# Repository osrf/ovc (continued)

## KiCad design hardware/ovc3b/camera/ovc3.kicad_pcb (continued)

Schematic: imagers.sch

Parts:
C16, C17, C20, C21: 1u; C_0402_1005Metric; MPN CL05A105KA5NQNC
C22, C23, C24, C25, C32, C33, C34, C35, C42, C43, C45, C46: 10u; C_0402_1005Metric; MPN CL05A106MP8NUB8
C26, C27, C28, C29, C30, C31, C36, C37, C38, C39, C40, C41, C44, C47, C48, C49, C50, C51, C54, C55, C56, C57, C58, C59, C60, C61, C62, C63, C64, C65: 100n; C_0402_1005Metric; MPN CL05F104ZO5NNNC
J1: LEFT_LENS; LENS_HOLDER_20MM_PT-LH010M; MPN DNP
J2: RIGHT_LENS; LENS_HOLDER_20MM_PT-LH010M; MPN DNP
J4: MIDDLE_LENS; LENS_HOLDER_20MM_PT-LH010M; MPN DNP
J11: CAM2_TIMING_DEBUG; PinHeader_1x05_P2.00mm_Vertical; MPN DNP
U1, U2: AR0144CS; BGA-72_9x8_5.545x5.565mm; MPN AR0144CSSM00SUKA0-CPBR2
U4: AR0144CS; BGA-72_9x8_5.545x5.565mm; MPN AR0144CSSC00SUKA0-CPBR2
U10, U12: LP5907MFX-2.8; SOT-23-5; MPN LP5907MFX-2.8/NOPB

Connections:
+1V2: C24.1, C26.1, C29.1, C31.1, C34.1, C36.1, C39.1, C41.1, C44.1, C46.1, C49.1, C51.1, C60.1, C61.1, C62.1, C63.1, C64.1, C65.1, U1.A3 (DVDD), U1.B2 (DVDD), U1.C5 (DVDD_PHY), U1.C6 (DVDD), U1.D8 (DVDD), U1.F2 (DVDD), U1.G4 (DVDD), U1.G5 (DVDD), U1.G6 (DVDD), U2.A3 (DVDD), U2.B2 (DVDD), U2.C5 (DVDD_PHY), U2.C6 (DVDD), U2.D8 (DVDD), U2.F2 (DVDD), U2.G4 (DVDD), U2.G5 (DVDD), U2.G6 (DVDD), U4.A3 (DVDD), U4.B2 (DVDD), U4.C5 (DVDD_PHY), U4.C6 (DVDD), U4.D8 (DVDD), U4.F2 (DVDD), U4.G4 (DVDD), U4.G5 (DVDD), U4.G6 (DVDD); also elsewhere on the board
+1V8: C25.1, C30.1, C35.1, C40.1, C45.1, C50.1, C57.1, C58.1, C59.1, U1.A2 (VDDIO), U1.B8 (VDDIO), U1.C2 (VDDIO), U1.C8 (VDDIO), U1.E3 (VDDIO), U2.A2 (VDDIO), U2.B8 (VDDIO), U2.C2 (VDDIO), U2.C8 (VDDIO), U2.E3 (VDDIO), U4.A2 (VDDIO), U4.B8 (VDDIO), U4.C2 (VDDIO), U4.C8 (VDDIO), U4.E3 (VDDIO); also elsewhere on the board
/imagers/CAM0_2V8: C17.1, C22.1, C23.1, C27.1, C28.1, C54.1, U1.F9 (VAA_PIX), U1.G2 (VAA), U1.G8 (VAA), U1.H1 (VAA), U1.H2 (VAA), U1.H8 (VAA), U1.H9 (VAA), U10.5
/imagers/CAM1_2V8: C21.1, C32.1, C33.1, C37.1, C38.1, C42.1, C43.1, C47.1, C48.1, C55.1, C56.1, U2.F9 (VAA_PIX), U2.G2 (VAA), U2.G8 (VAA), U2.H1 (VAA), U2.H2 (VAA), U2.H8 (VAA), U2.H9 (VAA), U4.F9 (VAA_PIX), U4.G2 (VAA), U4.G8 (VAA), U4.H1 (VAA), U4.H2 (VAA), U4.H8 (VAA), U4.H9 (VAA), U12.5
CAM0_CLK+: U1.A5 (CLK+); also elsewhere on the board
CAM0_CLK-: U1.B5 (CLK-); also elsewhere on the board
CAM0_D0+: U1.A6 (DATA0+); also elsewhere on the board
CAM0_D0-: U1.B6 (DATA0-); also elsewhere on the board
CAM0_D1+: U1.A4 (DATA1+)
CAM0_D1-: U1.B4 (DATA1-)
CAM0_EXTCLK_1V8: U1.B3 (EXTCLK); also elsewhere on the board
CAM0_SCL_1V8: U1.C7 (SCL); also elsewhere on the board
CAM0_SDA_1V8: U1.E6 (SDA); also elsewhere on the board
CAM0_TRIG_1V8: U1.E7 (TRIGGER); also elsewhere on the board
CAM0_nRESET_1V8: U1.G1 (~RESET); also elsewhere on the board
CAM1_CLK+: U2.A5 (CLK+); also elsewhere on the board
CAM1_CLK-: U2.B5 (CLK-); also elsewhere on the board
CAM1_D0+: U2.A6 (DATA0+); also elsewhere on the board
CAM1_D0-: U2.B6 (DATA0-); also elsewhere on the board
CAM1_D1+: U2.A4 (DATA1+)
CAM1_D1-: U2.B4 (DATA1-)
CAM1_EXTCLK_1V8: U2.B3 (EXTCLK); also elsewhere on the board
CAM1_SCL_1V8: U2.C7 (SCL); also elsewhere on the board
CAM1_SDA_1V8: U2.E6 (SDA); also elsewhere on the board
CAM1_TRIG_1V8: U2.E7 (TRIGGER); also elsewhere on the board
CAM1_nRESET_1V8: U2.G1 (~RESET); also elsewhere on the board
CAM2_CLK+: U4.A5 (CLK+); also elsewhere on the board
CAM2_CLK-: U4.B5 (CLK-); also elsewhere on the board
CAM2_D0+: U4.A6 (DATA0+); also elsewhere on the board
CAM2_D0-: U4.B6 (DATA0-); also elsewhere on the board
CAM2_D1+: U4.A4 (DATA1+)
CAM2_D1-: U4.B4 (DATA1-)
CAM2_EXTCLK_1V8: U4.B3 (EXTCLK); also elsewhere on the board
CAM2_FLASH_1V8: J11.3, U4.F6 (FLASH)
CAM2_SCL_1V8: J11.1, U4.C7 (SCL); also elsewhere on the board
CAM2_SDA_1V8: J11.2, U4.E6 (SDA); also elsewhere on the board
CAM2_TRIG_1V8: J11.4, U4.E7 (TRIGGER); also elsewhere on the board
CAM2_nRESET_1V8: U4.G1 (~RESET); also elsewhere on the board
GND: C16.2, C17.2, C20.2, C21.2, C22.2, C23.2, C24.2, C25.2, C26.2, C27.2, C28.2, C29.2, C30.2, C31.2, C32.2, C33.2, C34.2, C35.2, C36.2, C37.2, C38.2, C39.2, C40.2, C41.2, C42.2, C43.2, C44.2, C45.2, C46.2, C47.2, C48.2, C49.2, C50.2, C51.2, C54.2, C55.2, C56.2, C57.2, C58.2, C59.2, C60.2, C61.2, C62.2, C63.2, C64.2, C65.2, J1.1, J2.1, J4.1, J11.5, U1.A1 (DGND), U1.A8 (TEST), U1.B7 (SADDR), U1.D5 (DGND), U1.D6 (DGND), U1.D7 (~OUTPUT_EN), U1.D9 (AGND), U1.E8 (DGND), U1.F1 (DGND), U1.F7 (DGND), U1.F8 (DGND), U1.G3 (AGND), U1.G7 (AGND), U1.H3 (AGND), U1.H4 (DGND), U1.H5 (DGND), U1.H6 (DGND), U1.H7 (AGND), U2.A1 (DGND), U2.A8 (TEST), U2.B7 (SADDR), U2.D5 (DGND), U2.D6 (DGND), U2.D7 (~OUTPUT_EN), U2.D9 (AGND), U2.E8 (DGND), U2.F1 (DGND), U2.F7 (DGND), U2.F8 (DGND), U2.G3 (AGND), U2.G7 (AGND), U2.H3 (AGND), U2.H4 (DGND), U2.H5 (DGND), U2.H6 (DGND), U2.H7 (AGND), U4.A1 (DGND), U4.A8 (TEST), U4.B7 (SADDR), U4.D5 (DGND), U4.D6 (DGND), U4.D7 (~OUTPUT_EN), U4.D9 (AGND), U4.E8 (DGND), U4.F1 (DGND), U4.F7 (DGND), U4.F8 (DGND), U4.G3 (AGND), U4.G7 (AGND), U4.H3 (AGND), U4.H4 (DGND), U4.H5 (DGND), U4.H6 (DGND), U4.H7 (AGND), U10.2, U12.2; also elsewhere on the board

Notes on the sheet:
VDD is 1.2V, VAA is 2.8V, VDD_IO is 1.8V
RGB sensor

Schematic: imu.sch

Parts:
C11, C12, C13: 100n; C_0402_1005Metric; MPN CL05F104ZO5NNNC
U3: ICM-20948; InvenSense_QFN-24_3x3mm_P0.4mm; MPN ICM-20948

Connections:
+1V8: C11.1, U3.8 (VDDIO); also elsewhere on the board
GND: C11.2, C12.2, C13.2, U3.18 (GND), U3.20 (GND); also elsewhere on the board
ICM_IMU_INT1_1V8: U3.12 (INT1); also elsewhere on the board
ICM_IMU_SYNC_1V8: U3.11 (FSYNC); also elsewhere on the board
ICM_SPI_CLK_1V8: U3.23 (SCL/SCLK); also elsewhere on the board
ICM_SPI_CS_1V8: U3.22 (~CS); also elsewhere on the board
ICM_SPI_MISO_1V8: U3.9 (SDO/AD0); also elsewhere on the board
ICM_SPI_MOSI_1V8: U3.24 (SDA/SDI); also elsewhere on the board
unnamed: C13.1, U3.10 (REGOUT)

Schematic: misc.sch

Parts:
C10: 100n; C_0603_1608Metric; MPN CL10B104KB8NNNC
C80, C81: 100n; C_0402_1005Metric; MPN CL05F104ZO5NNNC
D1, D7: LED; LED_0402_1005Metric; MPN VLMS1500-GS08
D2, D8: LED; LED_0402_1005Metric; MPN VLMG1500-GS08
J5: LOW_SPEED_EXP; PinHeader_2x15_P1.27mm_Vertical; MPN DNP
J7: Micro_SD_Card_Det_Hirose_DM3BT; microSD_HC_Hirose_DM3BT-DSF-PEJS; MPN DM3BT-DSF-PEJS
R14, R15, R29, R30: 330R; R_0402_1005Metric; MPN ERJ-2GEJ331X
U9: ARJ11C-MBSAS-A-BA-7MU2; MPN ARJ11C-MBSAS-A-BA-7MU2
U13: TXS02612; TI_RTW0024B; MPN TXS02612RTWR

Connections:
+1V2: J5.12, J5.14; also elsewhere on the board
+1V8: J5.1, J5.2; also elsewhere on the board
/misc/LS_CLK: J7.5, U13.19 (CLKB0)
/misc/LS_CMD: J7.3, U13.23 (DAT2B0)
/misc/LS_DAT0: J7.7, U13.22 (DAT3B0)
/misc/LS_DAT1: J7.8, U13.20 (CMDB0)
/misc/LS_DAT2: J7.1, U13.18 (DAT0B0)
/misc/LS_DAT3: J7.2, U13.16 (DAT1B0)
ETH_VCC: C10.1, U9.5 (CT), U9.6 (CT); also elsewhere on the board
GND: C10.2, C80.2, C81.2, D1.1 (K), D2.1 (K), D7.1 (K), D8.1 (K), J5.4, J5.10, J5.16, J5.30, J7.6, J7.11, U9.11 (GRNYEL_C), U9.14 (GRN_C), U9.MNT, U9.SHLD, U13.2 (GND), U13.11 (GND), U13.24 (SEL), U13.25 (PAD); also elsewhere on the board
GPIO0: J5.3; also elsewhere on the board
GPIO1: J5.5; also elsewhere on the board
GPIO2: J5.7; also elsewhere on the board
GPIO3: J5.9; also elsewhere on the board
GPIO4: J5.11; also elsewhere on the board
GPIO5: J5.13; also elsewhere on the board
GPIO6: J5.15; also elsewhere on the board
GPIO7: J5.17; also elsewhere on the board
GPIO8: J5.19; also elsewhere on the board
GPIO9: J5.21; also elsewhere on the board
GPIO10: J5.23; also elsewhere on the board
GPIO11: J5.25; also elsewhere on the board
GPIO12: J5.18; also elsewhere on the board
GPIO13: J5.20; also elsewhere on the board
GPIO14: J5.22; also elsewhere on the board
GPIO15: J5.24; also elsewhere on the board
GPIO16: J5.26; also elsewhere on the board
GPIO17: J5.28; also elsewhere on the board
GPIO18: J5.27; also elsewhere on the board
GPIO19: J5.29; also elsewhere on the board
LED0: R14.2; also elsewhere on the board
LED1: R15.2; also elsewhere on the board
LED2: R29.2; also elsewhere on the board
LED3: R30.2; also elsewhere on the board
unnamed: D1.2 (A), R14.1
unnamed: D2.2 (A), R15.1
unnamed: D7.2 (A), R29.1
unnamed: D8.2 (A), R30.1
PHY_MDI0_N: U9.2 (TRD0-); also elsewhere on the board
PHY_MDI0_P: U9.1 (TRD0+); also elsewhere on the board
PHY_MDI1_N: U9.4 (TRD1-); also elsewhere on the board
PHY_MDI1_P: U9.3 (TRD1+); also elsewhere on the board
PHY_MDI2_N: U9.8 (TRD2-); also elsewhere on the board
PHY_MDI2_P: U9.7 (TRD2+); also elsewhere on the board
PHY_MDI3_N: U9.10 (TRD3-); also elsewhere on the board
PHY_MDI3_P: U9.9 (TRD3+); also elsewhere on the board
SD_CLK: U13.9 (CLKA); also elsewhere on the board
SD_CMD: U13.1 (DAT2A); also elsewhere on the board
SD_DAT0: U13.3 (DAT3A); also elsewhere on the board
SD_DAT1: U13.4 (CMDA); also elsewhere on the board
SD_DAT2: U13.6 (DAT0A); also elsewhere on the board
SD_DAT3: U13.7 (DAT1A); also elsewhere on the board

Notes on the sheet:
not enough easily-routed high-voltage i/o for now, so leaving the LEDs open...

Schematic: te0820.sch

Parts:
C14, C15, C53, C69, C70, C71, C72, C73, C74, C85: 100n; C_0402_1005Metric; MPN CL05F104ZO5NNNC
CONN1: Trenz_conn_dummy; MPN LSHM-130-04.0-L-DV-A-S-K-TR
CONN2, CONN3: Trenz_conn_dummy; MPN LSHM-150-04.0-L-DV-A-S-K-TR
J6: FRONT_PACK; PinHeader_2x08_P2.00mm_Vertical; MPN Sullins
M1: TE0820; MPN DNP
R9, R16, R17, R18, R19, R20: 2k2; R_0402_1005Metric; MPN RC0402FR-072K2L
R12, R13, R21, R22, R26: 10k; R_0402_1005Metric; MPN ERA-2AED103X
R27: 1k; R_0402_1005Metric; MPN ERJ-2RKF1001X
SW1: SW_DIP_x04; SW_DIP_SPSTx04_Slide_6.7x11.72mm_W8.61mm_P2.54mm_LowProfile; MPN 418121270804
U8: SN74AXC4T245; TSSOP-16_4.4x5mm_P0.65mm; MPN SN74AXC4T245PWR
U16: SN74AXCH8T245; TSSOP-24_4.4x7.8mm_P0.65mm; MPN SN74AXCH8T245PWR
U17, U18: TCA9803; VSSOP-8_3.0x3.0mm_P0.65mm; MPN TCA9803DGKR

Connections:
3V3_VOUT: M1.JB2.9 (3.3V), M1.JB2.11 (3.3V); also elsewhere on the board
+1V2: C14.1, C69.1, C70.1, C73.1, J6.4, M1.JB1.10 (VCC_66), M1.JB1.12 (VCC_66), M1.JB2.8 (VCCO_64), M1.JB2.10 (VCCO_64), R17.1, R18.1, R19.1, R20.1, U8.1 (VCCA), U8.3 (2DIR), U16.1 (VCCA), U16.2 (DIR1), U17.1 (VCCA), U17.5 (EN), U18.1 (VCCA), U18.5 (EN); also elsewhere on the board
+1V8: C15.1, C71.1, C72.1, C74.1, M1.JB1.40 (1.8V), M1.JB2.6 (VCCO_65), R9.1, R13.1, R16.1, R21.1, R22.1, U8.16 (VCCB), U16.23 (VCCB), U16.24 (VCCB), U17.8 (VCCB), U18.8 (VCCB); also elsewhere on the board
/te0820/CAM1_EXTCLK_1V2: M1.JB1.42 (G3_B66_L4_P), U16.8 (A6)
/te0820/CAM1_SCL_1V2: M1.JB1.34 (G5_B66_L6_P), R18.2, U17.2 (SCLA)
/te0820/CAM1_SDA_1V2: M1.JB1.32 (F5_B66_L6_N), R17.2, U17.3 (SDAA)
/te0820/CAM1_TRIG_1V2: M1.JB1.36 (C8_B66_L22_P), U16.10 (A8)
/te0820/CAM1_nRESET_1V2: M1.JB1.38 (B8_B66_L22_N), U16.9 (A7)
/te0820/CAM2_EXTCLK_1V2: M1.JB1.50 (B1_B66_L7_N), U16.4 (A2)
/te0820/CAM2_SCL_1V2: M1.JB1.84 (A1_B66_L8_N), R20.2, U18.2 (SCLA)
/te0820/CAM2_SDA_1V2: M1.JB1.82 (A2_B66_L8_P), R19.2, U18.3 (SDAA)
/te0820/CAM2_TRIG_1V2: M1.JB1.52 (C1_B66_L7_P), U16.3 (A1)
/te0820/CAM2_nRESET_1V2: M1.JB1.48 (C6_B66_L20_P), U16.5 (A3)
/te0820/DIPSWITCH: M1.JB3.47 (U9_B65_L2_P), R22.2, SW1.5
/te0820/ICM_IMU_INT1_1V2: M1.JB1.77 (A9_B66_L23_P), U8.5 (1A2)
/te0820/ICM_SPI_CLK_1V2: M1.JB1.44 (F3_B66_L4_N), U16.7 (A5)
/te0820/ICM_SPI_CS_1V2: M1.JB1.46 (B6_B66_L20_N), U16.6 (A4)
/te0820/ICM_SPI_MISO_1V2: M1.JB1.75 (A8_B66_L23_N), U8.4 (1A1)
/te0820/ICM_SPI_MOSI_1V2: M1.JB1.76 (C2_B66_L12_N), U8.7 (2A2)
/te0820/ICM_SPI_SYNC_1V2: M1.JB1.78 (C3_B66_L12_P), U8.6 (2A1)
/te0820/JTAGEN: M1.JB1.90 (JTAGEN), R21.2, SW1.6
/te0820/MODE: M1.JB1.31 (MODE), R13.2, SW1.7
/te0820/NOSEQ: M1.JB1.8 (NOSEQ), R12.2, SW1.8
BONUS1_CLK0+: M1.JB2.35 (AC9_B64_L1_P); also elsewhere on the board
BONUS1_CLK0-: M1.JB2.37 (AD9_B64_L1_N); also elsewhere on the board
BONUS1_CLK1+: M1.JB2.62 (AD2_B64_L16_P); also elsewhere on the board
BONUS1_CLK1-: M1.JB2.64 (AD1_B64_L16_N); also elsewhere on the board
BONUS1_DAT0+: M1.JB2.41 (AE9_B64_L2_P); also elsewhere on the board
BONUS1_DAT0-: M1.JB2.43 (AE8_B64_L2_N); also elsewhere on the board
BONUS1_DAT1+: M1.JB2.46 (AB2_B64_L17_P); also elsewhere on the board
BONUS1_DAT1-: M1.JB2.48 (AC2_B64_L17_N); also elsewhere on the board
BONUS1_EXTCLK: M1.JB2.44 (AB4_B64_L15_P); also elsewhere on the board
BONUS1_FLASH: M1.JB2.78 (AG5_B64_L10_N); also elsewhere on the board
BONUS1_RESET: M1.JB2.76 (AG6_B64_L10_P); also elsewhere on the board
BONUS1_SCL0: M1.JB2.56 (AB1_B64_L18_P); also elsewhere on the board
BONUS1_SCL1: M1.JB2.66 (AE3_B64_L21_P); also elsewhere on the board
BONUS1_SDA0: M1.JB2.58 (AC1_B64_L18_N); also elsewhere on the board
BONUS1_SDA1: M1.JB2.68 (AF3_B64_L21_N); also elsewhere on the board
BONUS1_TRIGGER: M1.JB2.42 (AB3_B64_L15_N); also elsewhere on the board
BONUS2_CLK0+: M1.JB1.67 (D7_B66_L13_P); also elsewhere on the board
BONUS2_CLK0-: M1.JB1.65 (D6_B66_L13_N); also elsewhere on the board
BONUS2_CLK1+: M1.JB1.39 (G8_B66_L16_P); also elsewhere on the board
BONUS2_CLK1-: M1.JB1.41 (F7_B66_L16_N); also elsewhere on the board
BONUS2_DAT0+: M1.JB1.62 (E5_B66_L14_P); also elsewhere on the board
BONUS2_DAT0-: M1.JB1.60 (D5_B66_L14_N); also elsewhere on the board
BONUS2_DAT1+: M1.JB1.47 (F8_B66_L17_P); also elsewhere on the board
BONUS2_DAT1-: M1.JB1.45 (E8_B66_L17_N); also elsewhere on the board
BONUS2_EXTCLK: M1.JB1.61 (E3_B66_L5_N); also elsewhere on the board
BONUS2_FLASH: M1.JB1.49 (G6_B66_L15_P); also elsewhere on the board
BONUS2_RESET: M1.JB1.37 (D9_B66_L18_N); also elsewhere on the board
BONUS2_SCL0: M1.JB1.59 (E4_B66_L5_P); also elsewhere on the board
BONUS2_SCL1: M1.JB1.55 (F2_B66_L3_P); also elsewhere on the board
BONUS2_SDA0: M1.JB1.57 (E2_B66_L3_N); also elsewhere on the board
BONUS2_SDA1: M1.JB1.51 (F6_B66_L15_N); also elsewhere on the board
BONUS2_TRIGGER: M1.JB1.35 (E9_B66_L18_P); also elsewhere on the board
BONUS3_CLK0+: M1.JB2.61 (AG9_B64_L7_P); also elsewhere on the board
BONUS3_CLK0-: M1.JB2.63 (AH9_B64_L7_N); also elsewhere on the board
BONUS3_CLK1+: M1.JB2.77 (AD7_B64_L4_P); also elsewhere on the board
BONUS3_CLK1-: M1.JB2.75 (AE7_B64_L4_N); also elsewhere on the board
BONUS3_DAT0+: M1.JB2.65 (AF8_B64_L8_P); also elsewhere on the board
BONUS3_DAT0-: M1.JB2.67 (AG8_B64_L8_N); also elsewhere on the board
BONUS3_DAT1+: M1.JB2.81 (AB7_B64_L5_P); also elsewhere on the board
BONUS3_DAT1-: M1.JB2.83 (AC7_B64_L5_N); also elsewhere on the board
BONUS3_EXTCLK: M1.JB2.31 (AB8_B64_L3_P); also elsewhere on the board
BONUS3_FLASH: M1.JB2.53 (AF5_B64_L12_N); also elsewhere on the board
BONUS3_RESET: M1.JB2.71 (AH8_B64_L9_P); also elsewhere on the board
BONUS3_SCL0: M1.JB2.33 (AC8_B64_L3_N); also elsewhere on the board
BONUS3_SCL1: M1.JB2.47 (AF6_B64_L11_N); also elsewhere on the board
BONUS3_SDA0: M1.JB2.45 (AF7_B64_L11_P); also elsewhere on the board
BONUS3_SDA1: M1.JB2.51 (AE5_B64_L12_P); also elsewhere on the board
BONUS3_TRIGGER: M1.JB2.73 (AH7_B64_L9_N); also elsewhere on the board
BONUS4_CLK0+: M1.JB2.72 (AE2_B64_L22_P); also elsewhere on the board
BONUS4_CLK0-: M1.JB2.74 (AF2_B64_L22_N); also elsewhere on the board
BONUS4_CLK1+: M1.JB2.82 (AG4_B64_L19_P); also elsewhere on the board
BONUS4_CLK1-: M1.JB2.84 (AH4_B64_L19_N); also elsewhere on the board
BONUS4_DAT0+: M1.JB2.95 (AH2_B64_L23_P); also elsewhere on the board
BONUS4_DAT0-: M1.JB2.97 (AH1_B64_L23_N); also elsewhere on the board
BONUS4_DAT1+: M1.JB2.86 (AG3_B64_L20_P); also elsewhere on the board
BONUS4_DAT1-: M1.JB2.88 (AH3_B64_L20_N); also elsewhere on the board
BONUS4_EXTCLK: M1.JB1.69 (C9_B66_L24_P); also elsewhere on the board
BONUS4_FLASH: M1.JB1.87 (B5_B66_L19_P); also elsewhere on the board
BONUS4_RESET: M1.JB1.97 (A3_B66_L9_N); also elsewhere on the board
BONUS4_SCL0: M1.JB1.71 (B9_B66_L24_N); also elsewhere on the board
BONUS4_SCL1: M1.JB1.81 (A6_B66_L21_N); also elsewhere on the board
BONUS4_SDA0: M1.JB1.79 (A7_B66_L21_P); also elsewhere on the board
BONUS4_SDA1: M1.JB1.85 (A5_B66_L19_N); also elsewhere on the board
BONUS4_TRIGGER: M1.JB1.99 (B3_B66_L9_P); also elsewhere on the board
CAM0_CLK+: M1.JB2.55 (AD5_B64_L13_P); also elsewhere on the board
CAM0_CLK-: M1.JB2.57 (AD4_B64_L13_N); also elsewhere on the board
CAM0_D0+: M1.JB2.52 (AC4_B64_L14_P); also elsewhere on the board
CAM0_D0-: M1.JB2.54 (AC3_B64_L14_N); also elsewhere on the board
CAM0_EXTCLK_1V8: M1.JB2.15 (P6_B65_L16_N); also elsewhere on the board
CAM0_SCL_1V8: M1.JB2.21 (L1_B65_L7_P), R16.2; also elsewhere on the board
CAM0_SDA_1V8: M1.JB2.23 (K1_B65_L7_N), R9.2; also elsewhere on the board
CAM0_TRIG_1V8: M1.JB2.27 (N6_B65_L15_N); also elsewhere on the board
CAM0_nRESET_1V8: M1.JB2.25 (N7_B65_L15_P); also elsewhere on the board
CAM1_CLK+: M1.JB1.70 (G1_B66_L1_P); also elsewhere on the board
CAM1_CLK-: M1.JB1.72 (F1_B66_L1_N); also elsewhere on the board
CAM1_D0+: M1.JB1.58 (E1_B66_L2_P); also elsewhere on the board
CAM1_D0-: M1.JB1.56 (D1_B66_L2_N); also elsewhere on the board
CAM1_EXTCLK_1V8: U16.16 (B6); also elsewhere on the board
CAM1_SCL_1V8: U17.7 (SCLB); also elsewhere on the board
CAM1_SDA_1V8: U17.6 (SDAB); also elsewhere on the board
CAM1_TRIG_1V8: U16.14 (B8); also elsewhere on the board
CAM1_nRESET_1V8: U16.15 (B7); also elsewhere on the board
CAM2_CLK+: M1.JB1.95 (B4_B66_L10_P); also elsewhere on the board
CAM2_CLK-: M1.JB1.93 (A4_B66_L10_N); also elsewhere on the board
CAM2_D0+: M1.JB1.68 (D4_B66_L11_P); also elsewhere on the board
CAM2_D0-: M1.JB1.66 (C4_B66_L11_N); also elsewhere on the board
CAM2_EXTCLK_1V8: U16.20 (B2); also elsewhere on the board
CAM2_SCL_1V8: U18.7 (SCLB); also elsewhere on the board
CAM2_SDA_1V8: U18.6 (SDAB); also elsewhere on the board
CAM2_TRIG_1V8: U16.21 (B1); also elsewhere on the board
CAM2_nRESET_1V8: U16.19 (B3); also elsewhere on the board
ETH_VCC: M1.JB1.13 (PHY_COM); also elsewhere on the board
FRONT_AUX0: J6.3, M1.JB2.85 (AB6_B64_L6_P)
FRONT_AUX1: J6.5, M1.JB2.87 (AC6_B64_L6_N)
FRONT_AUX2: J6.7, M1.JB2.91 (AF1_B64_L24_P)
FRONT_AUX3: J6.9, M1.JB2.93 (AG1_B64_L24_N)
FRONT_AUX4: J6.11, M1.JB2.99 (AH6_B64_T1)
FRONT_AUX5: J6.6, M1.JB2.90 (AD6_B64_T0)
GND: C14.2, C15.2, C53.2, C69.2, C70.2, C71.2, C72.2, C73.2, C74.2, C85.2, J6.2, M1.JB1.1 (GND), M1.JB1.7 (GND), M1.JB1.19 (GND), M1.JB1.25 (GND), M1.JB1.30 (GND), M1.JB1.33 (GND), M1.JB1.43 (GND), M1.JB1.53 (GND), M1.JB1.54 (GND), M1.JB1.63 (GND), M1.JB1.64 (GND), M1.JB1.73 (GND), M1.JB1.74 (GND), M1.JB1.83 (GND), M1.JB1.89 (GND), M1.JB2.19 (GND), M1.JB2.29 (GND), M1.JB2.39 (GND), M1.JB2.40 (GND), M1.JB2.49 (GND), M1.JB2.50 (GND), M1.JB2.59 (GND), M1.JB2.60 (GND), M1.JB2.69 (GND), M1.JB2.70 (GND), M1.JB2.79 (GND), M1.JB2.80 (GND), M1.JB2.89 (GND), M1.JB3.5 (GND), M1.JB3.6 (GND), M1.JB3.11 (GND), M1.JB3.12 (GND), M1.JB3.17 (GND), M1.JB3.18 (GND), M1.JB3.23 (GND), M1.JB3.24 (GND), M1.JB3.29 (GND), M1.JB3.30 (GND), M1.JB3.35 (GND), M1.JB3.36 (GND), M1.JB3.45 (GND), M1.JB3.46 (GND), M1.JB3.55 (GND), SW1.1, SW1.2, SW1.3, SW1.4, U8.2 (1DIR), U8.8 (GND), U8.9 (GND), U8.14 (OE#), U8.15 (OE#), U16.11 (DIR2), U16.12 (GND), U16.13 (GND), U16.22 (~OE), U17.4 (GND), U18.4 (GND); also elsewhere on the board
GPIO0: M1.JB2.12 (H9_B65_L24_P); also elsewhere on the board
GPIO1: M1.JB2.14 (H8_B65_L24_N); also elsewhere on the board
GPIO2: M1.JB2.16 (R8_B65_L4_P); also elsewhere on the board
GPIO3: M1.JB2.18 (T8_B65_L4_N); also elsewhere on the board
GPIO4: M1.JB2.22 (M6_B65_L14_P); also elsewhere on the board
GPIO5: M1.JB2.24 (L5_B65_L14_N); also elsewhere on the board
GPIO6: M1.JB2.26 (L3_B65_L12_P); also elsewhere on the board
GPIO7: M1.JB2.28 (L2_B65_L12_N); also elsewhere on the board
GPIO8: M1.JB2.32 (L8_B65_L18_N); also elsewhere on the board
GPIO9: M1.JB2.34 (M8_B65_L18_P); also elsewhere on the board
GPIO10: M1.JB2.36 (J7_B65_L21_P); also elsewhere on the board
GPIO11: M1.JB2.38 (H7_B65_L21_N); also elsewhere on the board
GPIO12: M1.JB3.44 (N8_B65_L17_N); also elsewhere on the board
GPIO13: M1.JB3.42 (N9_B65_L17_P); also elsewhere on the board
GPIO14: M1.JB3.40 (V8_B65_L3_N); also elsewhere on the board
GPIO15: M1.JB3.38 (U8_B65_L3_P); also elsewhere on the board
GPIO16: M1.JB3.37 (W8_B65_L1_P); also elsewhere on the board
GPIO17: M1.JB3.39 (Y8_B65_L1_N); also elsewhere on the board
GPIO18: M1.JB3.41 (R7_B65_L5_P); also elsewhere on the board
GPIO19: M1.JB3.43 (T7_B65_L5_N); also elsewhere on the board
ICM_IMU_INT1_1V8: U8.12 (1B2); also elsewhere on the board
ICM_IMU_SYNC_1V8: U8.11 (2B1); also elsewhere on the board
ICM_SPI_CLK_1V8: U16.17 (B5); also elsewhere on the board
ICM_SPI_CS_1V8: U16.18 (B4); also elsewhere on the board
ICM_SPI_MISO_1V8: U8.13 (1B1); also elsewhere on the board
ICM_SPI_MOSI_1V8: U8.10 (2B2); also elsewhere on the board
JTAG_TCK: J6.14, M1.JB2.100 (C_TCK)
JTAG_TDI: J6.12, M1.JB2.96 (C_TDI)
JTAG_TDO: J6.13, M1.JB2.98 (C_TDO)
JTAG_TMS: J6.15, M1.JB2.94 (C_TMS)
LED0: M1.JB1.94 (J15_MIO27); also elsewhere on the board
LED1: M1.JB1.96 (L15_MIO26); also elsewhere on the board
LED2: M1.JB1.98 (G16_MIO29); also elsewhere on the board
LED3: M1.JB1.100 (K15_MIO28); also elsewhere on the board
unnamed: M1.JB3.52 (OTG-ID), R27.2
unnamed: M1.JB3.56 (USB-VBUS), R26.2
PHY_MDI0_N: M1.JB1.5 (PHY_MDI0_N); also elsewhere on the board
PHY_MDI0_P: M1.JB1.3 (PHY_MDI0_P); also elsewhere on the board
PHY_MDI1_N: M1.JB1.11 (PHY_MDI1_N); also elsewhere on the board
PHY_MDI1_P: M1.JB1.9 (PHY_MDI1_P); also elsewhere on the board
PHY_MDI2_N: M1.JB1.17 (PHY_MDI2_N); also elsewhere on the board
PHY_MDI2_P: M1.JB1.15 (PHY_MDI2_P); also elsewhere on the board
PHY_MDI3_N: M1.JB1.23 (PHY_MDI3_N); also elsewhere on the board
PHY_MDI3_P: M1.JB1.21 (PHY_MDI3_P); also elsewhere on the board
ROOT_RX: J6.10, M1.JB1.91 (F16_MIO30)
ROOT_TX: J6.8, M1.JB1.86 (H16_MIO31)
SD_CLK: M1.JB1.28 (L21_SD_CLK); also elsewhere on the board
SD_CMD: M1.JB1.26 (M19_SD_CMD); also elsewhere on the board
SD_DAT0: M1.JB1.24 (L20_SD_DAT0); also elsewhere on the board
SD_DAT1: M1.JB1.22 (H21_SD_DAT1); also elsewhere on the board
SD_DAT2: M1.JB1.20 (J21_SD_DAT2); also elsewhere on the board
SD_DAT3: M1.JB1.18 (M18_SD_DAT3); also elsewhere on the board
USB2_D+: M1.JB3.48 (OTG-D_P); also elsewhere on the board
USB2_D-: M1.JB3.50 (OTG-D_N); also elsewhere on the board
USB3_RX+: M1.JB3.19 (D27_B505_RX1_P); also elsewhere on the board
USB3_RX-: M1.JB3.21 (D28_B505_RX1_N); also elsewhere on the board
USB3_TX+: M1.JB3.22 (D24_B505_TX1_N); also elsewhere on the board
USB3_TX-: M1.JB3.20 (D23_B505_TX1_P); also elsewhere on the board
USB_SCL: M1.JB1.92 (J16_MIO32); also elsewhere on the board
USB_SDA: M1.JB1.88 (L16_MIO33); also elsewhere on the board
VBUS: R26.1; also elsewhere on the board
VCC_JTAG: J6.16, M1.JB2.92 (3.3VIN)

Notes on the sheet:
boot-select DIP switch
IO banks voltages
https://wiki.trenz-electronic.de/display/PD/TE0820+TRM
MIPI CLK
Bank 65 needs to be >1v5 for the Si5338
always enabled, A->B
right-hand side level shifters
always enabled
pullup provided on TE0820
available MIPI clock: AC9, AD7, AG4, AE2, AG9, AG6, AD2, AD5
1DIR = B->A 2DIR = A->B
always device mode
MISO
NRST
MOSI
SCK
SYNC

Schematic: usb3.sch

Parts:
C1, C2, C3, C52, C67: 1u; C_0402_1005Metric; MPN CL05A105KA5NQNC
C4, C5, C6, C7, C8, C66, C84: 100n; C_0402_1005Metric; MPN CL05F104ZO5NNNC
C9: 3n3; C_0402_1005Metric; MPN CL05B332KB5NNNC
C18: 680u; CP_Elec_6.3x7.7; voltage 6.3V; MPN EEE-FTJ681XAP
C19: 4u7; C_0603_1608Metric; voltage 25V; MPN CL10A475KA8NQNC
C68: 10u; C_0402_1005Metric; MPN CL05A106MP8NUB8
C75, C76: 22u; C_0603_1608Metric; MPN GRM188R60J226MEA0D
C77: 100u; C_1206_3216Metric; MPN GRM31CR60J107ME39K
C78, C82: 22u; C_1206_3216Metric; MPN CL31A226KAHNNNE
C79, C83: 47u; C_1206_3216Metric; MPN CL31A476MQHNNNE
C86, C87: 100n; C_0402_1005Metric; Voltage 50 V; MPN GRM155R61H104KE19D
D3: LED; LED_0402_1005Metric; MPN VLMG1500-GS08
D4: ESDA25W; SOT-23; MPN ESDA25W
D5: SMBJ22A; D_SMB; MPN SMBJ22A
D6: SDMK0340L-7-F; D_SOD-323; MPN SDMK0340L-7-F
D9: PMEG3030EP,115; D_SOD-128; MPN PMEG3030EP,115
J3: USB_C_Receptacle; USB_C_Receptacle_Wurth_632723300011; MPN 632723300011
J8: AUX_PWR; Molex_Nano-Fit_105313-xx02_1x02_P2.50mm_Horizontal; MPN 1053131102
J12: I2C_DEBUG; PinHeader_1x04_P2.00mm_Vertical; MPN DNP
Q1, Q2: SI2369DS; SOT-23; MPN SI2369DS-T1-GE3
R1, R4, R6: 100k; R_0402_1005Metric; MPN ERA-2AED104X
R2, R3: 10k; R_0402_1005Metric; MPN ERA-2AED103X
R5: 22k; R_0402_1005Metric; MPN ERJ-2RKF2202X
R7: 100R; R_0402_1005Metric; MPN ERA-2AED101X
R8: 1k; R_0603_1608Metric; MPN ESR03EZPJ102
R10: 90k9; R_0402_1005Metric; MPN ERA-2AEB9092X
R11: 316R; R_0402_1005Metric; MPN ERJ-2RKF3160X
R23: 330R; R_0402_1005Metric; MPN ERJ-2GEJ331X
R24: 470; R_0402_1005Metric; MPN ERJ-2RKF4700X
R25: 1k; R_0402_1005Metric; MPN ERJ-2RKF1001X
R28: 22k1; R_0402_1005Metric; MPN ERJ-2RKF2202X
R31, R33: 143k; R_0402_1005Metric
R32, R34: 10k; R_0402_1005Metric
U5: STUSB4500; QFN-24-1EP_4x4mm_P0.5mm_EP2.7x2.7mm; MPN STUSB4500QTR
U6: HD3SS3202; TI_R_PUQFN_N16; MPN HD3SS3202IRSVR
U7: LMZ31707; TI_RVQ_42; MPN LMZ31707RVQR
U11: TPS2121; Texas_VQFN-HR-12_2x2.5_Pitch0.5mm; MPN TPS2121RUXR
U14: TVS1800DRV; WSON-6-1EP_2x2mm_P0.65mm_EP1x1.6mm; MPN TVS1800DRVR
U15: EN5322QI; Converter_DCDC_Intel_QFN-24_4x6mm_P0.65mm_ThermalVias; MPN EN5322QI

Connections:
3V3_VOUT: C84.2, R2.1, R3.1, R6.1, U6.3 (VCC); also elsewhere on the board
+1V2: C75.1, C76.1, U15.4 (VOUT), U15.5 (VOUT), U15.6 (VOUT), U15.7 (VOUT), U15.13 (VSENSE); also elsewhere on the board
+1V8: U15.18 (ENABLE); also elsewhere on the board
/usb3/1V2: C2.1, U5.21 (VREG_1V2)
/usb3/2V7: C1.1, U5.23 (VREG_2V7)
/usb3/ABSIDE: R6.2, U5.17 (A_B_SIDE), U6.6 (SEL)
/usb3/AUX_PWR: D9.2, J8.1, U14.4, U14.5, U14.6
/usb3/CONN_CC1: D4.1 (K), J3.A5 (CC1), U5.1 (CC1DB), U5.2 (CC1)
/usb3/CONN_CC2: D4.2 (K), J3.B5 (CC2), U5.4 (CC2), U5.5 (CC2DB)
/usb3/CONN_RX1+: J3.B11 (RX1+), U6.8 (C1+)
/usb3/CONN_RX1-: J3.B10 (RX1-), U6.7 (C1-)
/usb3/CONN_RX2+: J3.A11 (RX2+), U6.12 (B1+)
/usb3/CONN_RX2-: J3.A10 (RX2-), U6.11 (B1-)
/usb3/CONN_SBU1: J3.A8 (SBU1)
/usb3/CONN_SBU2: J3.B8 (SBU2)
/usb3/CONN_TX1+: C6.2, J3.A2 (TX1+)
/usb3/CONN_TX1-: C8.2, J3.A3 (TX1-)
/usb3/CONN_TX2+: C5.2, J3.B2 (TX2+)
/usb3/CONN_TX2-: C7.2, J3.B3 (TX2-)
/usb3/CONN_VBUS: C19.1, D5.1 (A1), D6.2 (A), J3.A4 (VBUS), J3.A9 (VBUS), J3.B4 (VBUS), J3.B9 (VBUS), Q1.3 (D), R24.1
/usb3/DISCH: R8.2, U5.9 (DISCH)
/usb3/GATES: Q1.1 (G), Q2.1 (G), R4.2, R5.1, R7.2
/usb3/PH: U7.10 (PH), U7.13 (PH), U7.14 (PH), U7.15 (PH), U7.16 (PH), U7.17 (PH), U7.18 (PH), U7.19 (PH), U7.42 (PH)
/usb3/PWGND: C9.2, R10.2, R11.2, U7.2 (AGND), U7.23 (AGND), U7.29 (STSEL)
/usb3/RESET: R1.1, U5.6 (RESET)
/usb3/T1+: C6.1, U6.9 (C0-)
/usb3/T1-: C8.1, U6.10 (C0+)
/usb3/T2+: C5.1, U6.13 (B0-)
/usb3/T2-: C7.1, U6.14 (B0+)
/usb3/VAUX: C87.1, D9.1, R31.1, U11.7 (IN1)
GND: C1.2, C2.2, C3.2, C18.2, C19.2, C52.2, C66.2, C67.2, C68.2, C75.2, C76.2, C77.2, C78.2, C79.2, C82.2, C83.2, C84.1, C86.2, C87.2, D3.1 (K), D4.3 (A), D5.2 (A2), J3.A1 (GND), J3.A12 (GND), J3.B1 (GND), J3.B12 (GND), J3.S1 (SHIELD), J8.2, J12.4, R1.2, R28.2, R32.2, R34.2, U5.10 (GND), U5.12 (ADDR0), U5.13 (ADDR1), U5.25 (PAD), U6.2 (GND), U6.15 (~OE), U7.20 (PGND), U7.21 (PGND), U7.31 (PGND), U7.32 (PGND), U7.33 (PGND), U11.3 (CP2), U11.6 (PR1), U11.9 (ST), U11.12 (GND), U14.1, U14.2, U14.3, U14.7, U15.2 (PGND), U15.3 (PGND), U15.8 (PGND), U15.9 (PGND), U15.11 (VS1), U15.15 (AGND), U15.25 (PGND); also elsewhere on the board
unnamed: C3.1, Q1.2 (S), Q2.2 (S), R4.1, U5.24 (VDD)
unnamed: C4.2, R7.1
unnamed: C9.1, U7.28 (SS/TR)
unnamed: C52.1, D6.1 (K), R24.2, R25.1
unnamed: C66.1, U11.11 (SS)
unnamed: D3.2 (A), R23.2
unnamed: R5.2, U5.16 (VBUS_EN_SINK)
unnamed: R10.1, U7.22 (RT/CLK)
unnamed: R11.1, U7.26 (VADJ)
unnamed: R25.2, U5.18 (VBUS_VS_DISCH)
unnamed: R28.1, U11.10 (ILIM)
unnamed: R31.2, R32.1, U11.5 (OV1)
unnamed: R33.2, R34.1, U11.4 (OV2)
USB2_D+: J3.A6 (D+), J3.B6 (D+); also elsewhere on the board
USB2_D-: J3.A7 (D-), J3.B7 (D-); also elsewhere on the board
USB3_RX+: U6.4 (A1+); also elsewhere on the board
USB3_RX-: U6.5 (A1-); also elsewhere on the board
USB3_TX+: U6.16 (A0+); also elsewhere on the board
USB3_TX-: U6.1 (A0-); also elsewhere on the board
USB_SCL: J12.2, R2.2, U5.7 (SCL); also elsewhere on the board
USB_SDA: J12.3, R3.2, U5.8 (SDA); also elsewhere on the board
VBUS: C4.1, C86.1, Q2.3 (D), R8.1, R33.1, U11.2 (IN2); also elsewhere on the board
VCC: C78.1, C82.1, U7.1 (PVIN), U7.3 (VIN), U7.11 (PVIN), U7.12 (PVIN), U7.39 (PVIN), U7.40 (PVIN), U11.1 (OUT), U11.8 (OUT)

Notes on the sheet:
SBU not used
polarity swap OK
TPS2121 over-voltage cutoff set to 16 V
TVS1800 working voltage 18V, clamps by 24 V
USB type-C mux options: HD3SS3202 (passive) PTN36043 (active) TUSB1042I (active)
Current limit set at 4.5A Switches to IN1 when IN1 > IN2

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
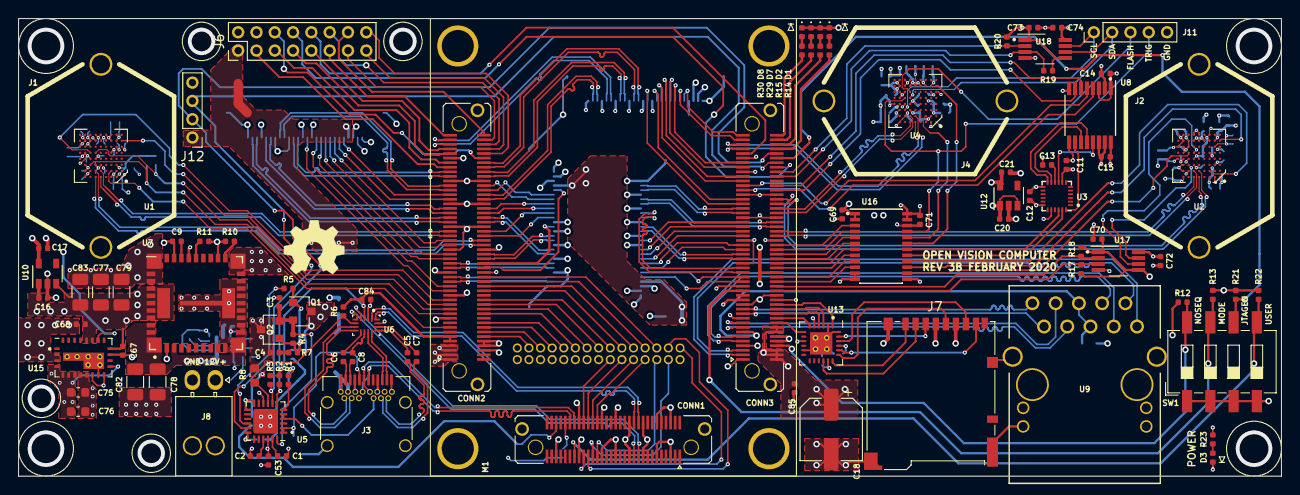
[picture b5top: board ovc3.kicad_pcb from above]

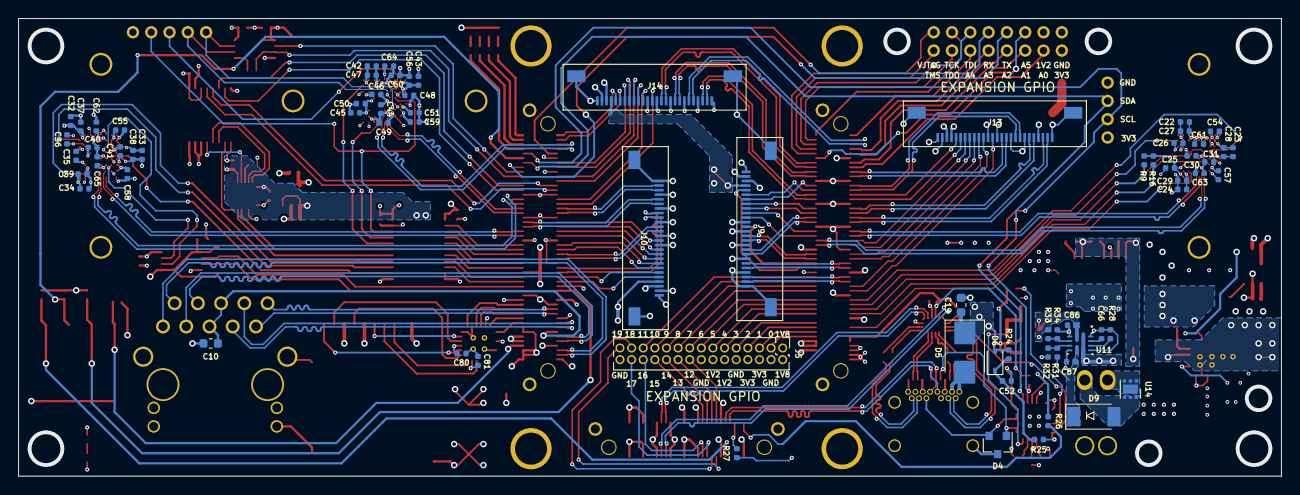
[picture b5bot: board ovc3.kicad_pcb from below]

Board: 6 copper layers, 138.0 x 50.0 mm, 167 parts (72 on the bottom side), 238 nets.

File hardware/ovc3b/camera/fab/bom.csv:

# Bill of Materials for 'ovc3' rev.a
# Schematic date: Fri Feb 21 16:22:17 2020
Line Item,Quantity,Designator,Footprint,Value,Tolerance,Thermal,Voltage,Manufacturer,Manufacturer Part Number,Distributor,Distributor Part Number,Substitution OK?
1,9,"C1,C2,C3,C16,C17,C20,C21,C52,C67",Capacitor_SMD:C_0402_1005Metric,1u,,,,Samsung,CL05A105KA5NQNC,Digikey,1276-1445-1-ND,
2,52,"C4,C5,C6,C7,C8,C11,C12,C13,C14,C15,C26,C27,C28,C29,C30,C31,C36,C37,C38,C39,C40,C41,C44,C47,C48,C49,C50,C51,C53,C54,C55,C56,C57,C58,C59,C60,C61,C62,C63,C64,C65,C66,C69,C70,C71,C72,C73,C74,C80,C81,C84,C85",Capacitor_SMD:C_0402_1005Metric,100n,,,,Samsung,CL05F104ZO5NNNC,Digikey,1276-1004-1-ND,
3,1,"C9",Capacitor_SMD:C_0402_1005Metric,3n3,,,,Samsung,CL05B332KB5NNNC,Digikey,1276-1552-2-ND,
4,1,"C10",Capacitor_SMD:C_0603_1608Metric,100n,,,,Samsung,CL10B104KB8NNNC,Digikey,1276-1000-1-ND,
5,1,"C18",Capacitor_SMD:CP_Elec_6.3x7.7,680u,,,6.3V,Panasonic,EEE-FTJ681XAP,Digikey,P15097TR-ND,
6,1,"C19",Capacitor_SMD:C_0603_1608Metric,4u7,,,25V,Samsung,CL10A475KA8NQNC,Digikey,1276-1900-1-ND,
7,13,"C22,C23,C24,C25,C32,C33,C34,C35,C42,C43,C45,C46,C68",Capacitor_SMD:C_0402_1005Metric,10u,,,,Samsung,CL05A106MP8NUB8,Digikey,1276-6830-1-ND,
8,2,"C75,C76",Capacitor_SMD:C_0603_1608Metric,22u,,,,Murata,GRM188R60J226MEA0D,Digikey,490-7611-1-ND,
9,1,"C77",Capacitor_SMD:C_1206_3216Metric,100u,,,,Murata,GRM31CR60J107ME39K,Digikey,490-7217-1-ND,
10,2,"C78,C82",Capacitor_SMD:C_1206_3216Metric,22u,,,,Samsung,CL31A226KAHNNNE,Digikey,1276-3047-1-ND,
11,2,"C79,C83",Capacitor_SMD:C_1206_3216Metric,47u,,,,Samsung,CL31A476MQHNNNE,Digikey,1276-1167-1-ND,
12,2,"D1,D7",LED_SMD:LED_0402_1005Metric,LED,,,,Vishay,VLMS1500-GS08,Digikey,VLMS1500-GS08CT-ND,
13,3,"D2,D3,D8",LED_SMD:LED_0402_1005Metric,LED,,,,Vishay,VLMG1500-GS08,Digikey,VLMG1500-GS08CT-ND,
14,1,"D4",Package_TO_SOT_SMD:SOT-23,ESDA25W,,,,ST,ESDA25W,Digikey,497-6689-1-ND,
15,1,"D5",Diode_SMD:D_SMB,SMBJ22A,,,,Bourns,SMBJ22A,Digikey,SMBJ22ABCT-ND,
16,1,"D6",Diode_SMD:D_SOD-323,SDMK0340L-7-F,,,,Diodes Inc,SDMK0340L-7-F,Digikey,SDMK0340L-FDICT-ND,
17,5,"J1,J2,J4,J5,J11",LensHolder:LENS_HOLDER_20MM_PT-LH010M,MIDDLE_LENS,,,,DNP,DNP,DNP,DNP,
18,1,"J3",USB:USB_C_Receptacle_Wurth_632723300011,USB_C_Receptacle,,,,Wurth,632723300011,Digikey,732-9618-1-ND,
19,1,"J6",Connector_PinHeader_2.00mm:PinHeader_2x08_P2.00mm_Vertical,FRONT_PACK,,,,NRPN082PAEN-RC,Sullins,Digikey,S5801-08-ND,
20,1,"J7",Connector_Card:microSD_HC_Hirose_DM3BT-DSF-PEJS,Micro_SD_Card_Det_Hirose_DM3BT,,,,Hirose,DM3BT-DSF-PEJS,Digikey,HR1942CT-ND,
21,1,"J8",Connector_Molex:Molex_Nano-Fit_105313-xx02_1x02_P2.50mm_Horizontal,AUX_PWR,,,,Molex,1053131102,Digikey,WM16893-ND,
22,4,"J9,J10,J13,J14",Connectors_OSRF:MOLEX_505110_2691,BONUS1,,,,Molex,5051102691,Digikey,WM24281CT-ND,
23,1,"J12",Connector_PinHeader_2.00mm:PinHeader_1x04_P2.00mm_Vertical,I2C_DEBUG,,,,DNP,DNP,unknown,DNP,
24,1,"CONN1",undefined,Trenz_conn_dummy,,,,Samtec,LSHM-130-04.0-L-DV-A-S-K-TR,Digikey,SAM9034CT-ND,
25,2,"CONN2,CONN3",undefined,Trenz_conn_dummy,,,,Samtec,LSHM-150-04.0-L-DV-A-S-K-TR,Digikey,SAM9033CT-ND,
26,2,"Q1,Q2",Package_TO_SOT_SMD:SOT-23,SI2369DS,,,,Vishay,SI2369DS-T1-GE3,Digikey,SI2369DS-T1-GE3CT-ND,
27,3,"R1,R4,R6",Resistor_SMD:R_0402_1005Metric,100k,,,,Panasonic,ERA-2AED104X,Digikey,P100KDECT-ND,
28,7,"R2,R3,R12,R13,R21,R22,R26",Resistor_SMD:R_0402_1005Metric,10k,,,,Panasonic,ERA-2AED103X,Digikey,P10KDECT-ND,
29,2,"R5,R28",Resistor_SMD:R_0402_1005Metric,22k,,,,Panasonic,ERJ-2RKF2202X,Digikey,P22.0KLCT-ND,
30,1,"R7",Resistor_SMD:R_0402_1005Metric,100R,,,,Panasonic,ERA-2AED101X,Digikey,P100DECT-ND,
31,1,"R8",Resistor_SMD:R_0603_1608Metric,1k,,,,Rohm,ESR03EZPJ102,Digikey,RHM1.0KDCT-ND,
32,6,"R9,R16,R17,R18,R19,R20",Resistor_SMD:R_0402_1005Metric,2k2,,,,Yageo,RC0402FR-072K2L,Digikey,311-2.20KLRCT-ND,
33,1,"R10",Resistor_SMD:R_0402_1005Metric,90k9,,,,Panasonic,ERA-2AEB9092X,Digikey,P90.9KDCCT-ND,
34,1,"R11",Resistor_SMD:R_0402_1005Metric,316R,,,,Panasonic,ERJ-2RKF3160X,Digikey,P316LCT-ND,
35,5,"R14,R15,R23,R29,R30",Resistor_SMD:R_0402_1005Metric,330R,,,,Panasonic,ERJ-2GEJ331X,Digikey,P330JCT-ND,
36,1,"R24",Resistor_SMD:R_0402_1005Metric,470,,,,Panasonic,ERJ-2RKF4700X,Digikey,P470LCT-ND,
37,2,"R25,R27",Resistor_SMD:R_0402_1005Metric,1k,,,,Panasonic,ERJ-2RKF1001X,Digikey,P1.00KLCT-ND,
38,2,"U1,U2",ONSemi:BGA-72_9x8_5.545x5.565mm,AR0144CS,,,,ON Semiconductor,AR0144CSSM00SUKA0-CPBR2,Digikey,AR0144CSSM00SUKA0-CPBR2OS-ND,
39,1,"U3",Sensor_Motion:InvenSense_QFN-24_3x3mm_P0.4mm,ICM-20948,,,,TDK InvenSense,ICM-20948,Mouser,410-ICM-20948,
40,1,"U4",ONSemi:BGA-72_9x8_5.545x5.565mm,AR0144CS,,,,ON Semiconductor,AR0144CSSC00SUKA0-CPBR2,Digikey,AR0144CSSC00SUKA0-CPBR2OS-ND,
41,1,"U5",Package_DFN_QFN:QFN-24-1EP_4x4mm_P0.5mm_EP2.7x2.7mm,STUSB4500,,,,STMicroelectronics,STUSB4500QTR,Digikey,497-18060-1-ND,
42,1,"U6",USB:TI_R_PUQFN_N16,HD3SS3202,,,,Texas Instruments,HD3SS3202IRSVR,Digikey,296-51121-1-ND,
43,1,"U7",DCDC:TI_RVQ_42,LMZ31707,,,,Texas Instruments,LMZ31707RVQR,Digikey,296-37921-1-ND,
44,1,"U8",Package_SO:TSSOP-16_4.4x5mm_P0.65mm,SN74AXC4T245,,,,Texas Instruments,SN74AXC4T245PWR,Digikey,296-53472-1-ND,
45,1,"U9",Ethernet:ARJ11C-MBSAS-A-BA-7MU2,ARJ11C-MBSAS-A-BA-7MU2,,,,Abracon,ARJ11C-MBSAS-A-BA-7MU2,Mouser,815-RJ1CMBSASABA7MU2,
46,2,"U10,U12",Package_TO_SOT_SMD:SOT-23-5,LP5907MFX-2.8,,,,Texas Instruments,LP5907MFX-2.8/NOPB,Digikey,296-39063-1-ND,
47,1,"U11",TI:Texas_VQFN-HR-12_2x2.5_Pitch0.5mm,TPS2121,,,,Texas Instruments,TPS2121RUXR,Digikey,296-53410-1-ND,
48,1,"U13",WQFN:TI_RTW0024B,TXS02612,,,,Texas Instruments,TXS02612RTWR,Digikey,296-23869-1-ND,
49,1,"U15",DCDC:Converter_DCDC_Intel_QFN-24_4x6mm_P0.65mm_ThermalVias,EN5322QI,,,,Intel,EN5322QI,Digikey,544-2849-1-ND,
50,1,"U16",Package_SO:TSSOP-24_4.4x7.8mm_P0.65mm,SN74AXCH8T245,,,,Texas Instruments,SN74AXCH8T245PWR,Digikey,296-50281-1-ND,
51,2,"U17,U18",Package_SO:VSSOP-8_3.0x3.0mm_P0.65mm,TCA9803,,,,Texas Instruments,TCA9803DGKR,Digikey,296-47829-1-ND,
52,1,"SW1",Button_Switch_SMD:SW_DIP_SPSTx04_Slide_6.7x11.72mm_W8.61mm_P2.54mm_LowProfile,SW_DIP_x04,,,,Wurth,418121270804,Digikey,732-6963-1-ND,
